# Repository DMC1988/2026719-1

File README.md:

🇬🇧 [English](README.md) | 🇦🇷 [Español](README.es.md)

# Optical Sensor for bill-counting Machine — NYQUEN LABS

Custom replacement PCB and 3D-printed mounting bracket for a discontinued optical encoder sensor board used in a bill-counting machine. See `REV_CONVENTION.md` for the full revision convention (rev A/B/C) and `CHANGELOG.md` for this project's revision history.

## Project Overview

**Problem:** the machine's optical encoder sensor board periodically stopped functioning, taking the counting machine out of service. The original board was difficult to source as a spare part.

**Solution:** reverse-engineered the sensor board's electrical interface, designed a drop-in replacement PCB (low-voltage signal board, no mains exposure), designed and 3D-printed a mounting bracket matching the original mounting geometry, and produced a batch of 50 units for the client's spare-parts inventory.

**Client:** industrial operator of cash-handling / bill-counting equipment (name withheld — this project predates NYQUEN LABS as a formal practice).

More details in `docs/case-study.docx`.

## Images

<!-- Replace the paths below with the actual image filenames once added to 3d-renders/. Recommended formats: .jpg/.png, keep file sizes reasonable (they're tracked via Git LFS). -->

**Finished project:**

**Render:**

## Folder Structure

```
.
├── hardware/               # KiCad project (schematic, PCB, project-specific libraries)
│   └── libraries/          # Project-specific symbol/footprint libs
├── mechanical/             # FreeCAD, STEP, 3D-printed bracket (Git LFS)
├── firmware/               # Not applicable to this project (kept for template consistency)
├── fabrication-outputs/    # Snapshots of Gerbers/BOM/Pick&Place per revision
│   └── revA/
├── docs/                   # Case study, datasheets, validation notes (Git LFS for PDFs)
├── 3d-renders/             # Photos/renders for portfolio use (Git LFS)
├── scripts/                # Setup/utility scripts (see below)
├── REV_CONVENTION.md
├── CHANGELOG.md
├── .gitignore
└── .gitattributes
```

## About NYQUEN LABS

Hardware, firmware, and mechanical design services. Contact: damian.m.caputo@gmail.com

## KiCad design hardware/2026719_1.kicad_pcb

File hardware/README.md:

# hardware/

Proyecto KiCad de este repo (.kicad_pro, .kicad_sch, .kicad_pcb).

- `libraries/` — símbolos/footprints

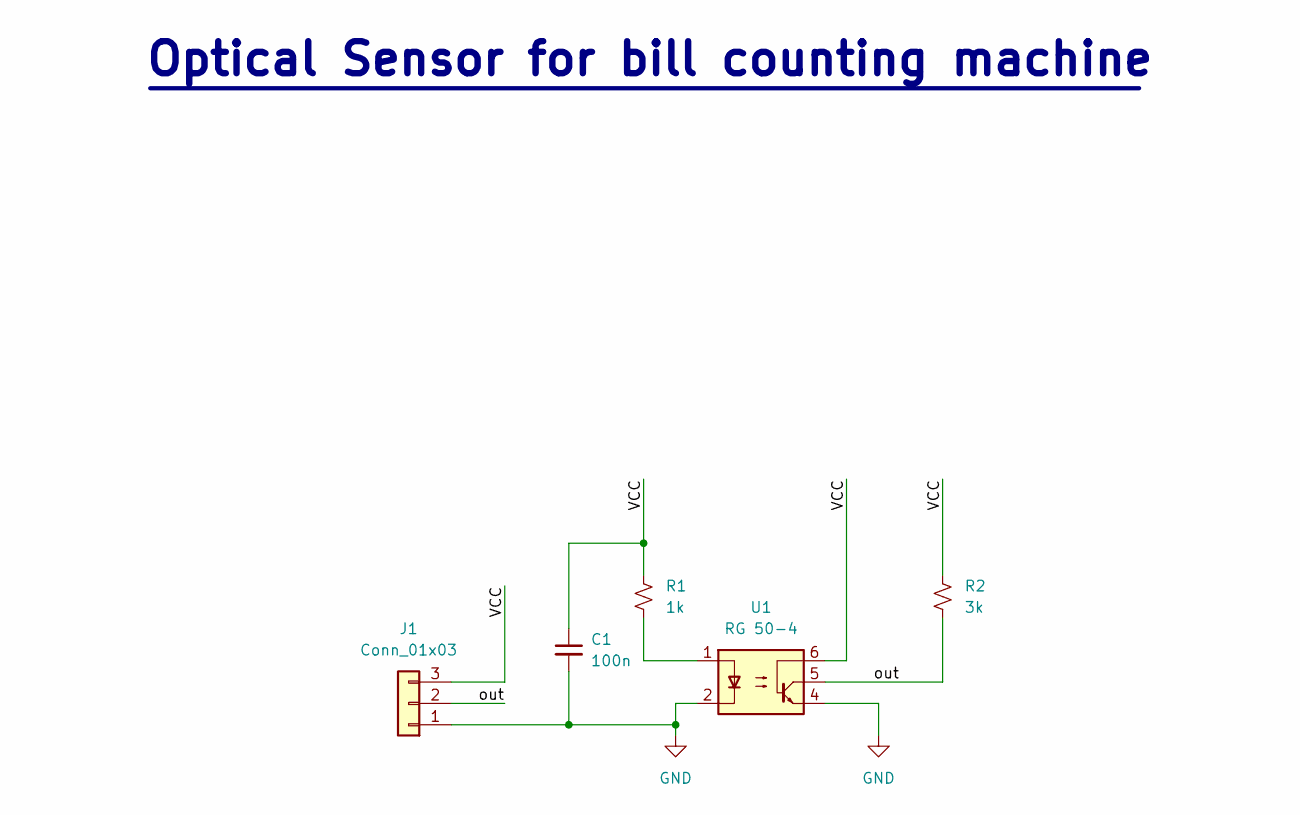
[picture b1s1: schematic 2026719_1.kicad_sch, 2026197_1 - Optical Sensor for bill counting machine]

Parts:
C1: 100n; C_0805_2012Metric
J1: Conn_01x03; JST_PH_B3B-PH-K_1x03_P2.00mm_Vertical
R1: 1k; R_0805_2012Metric
R2: 3k; R_0805_2012Metric
U1: RG 50-4; TCRT1010_VIS

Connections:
/VCC: C1.1, J1.3, R1.2, R2.1, U1.6
/out: J1.2, R2.2, U1.5
GND: C1.2, J1.1, U1.2, U1.4
unnamed: R1.1, U1.1

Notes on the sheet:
Optical Sensor for bill counting machine

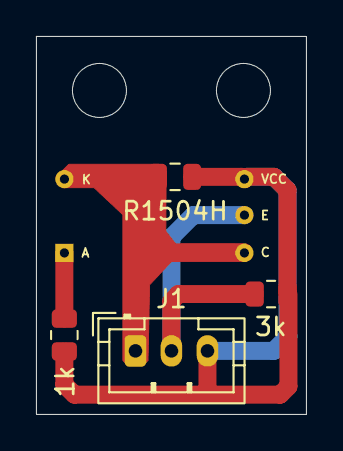
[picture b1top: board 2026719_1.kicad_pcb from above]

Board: 2 copper layers, 15.0 x 21.0 mm, 5 parts (1 on the bottom side), 4 nets.
